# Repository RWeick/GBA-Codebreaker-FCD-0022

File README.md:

# Blaze Xploder SP and Codebreaker FCD-0022
The full schematic, PCB, and flash dumps of the GBA Codebreaker and Xploder SP. Both use the same PCB and CPLD. The original PCB is a 4-layer PCB, though it isn't necessary in order to route everything.

PCB Thickness: 0.8 mm

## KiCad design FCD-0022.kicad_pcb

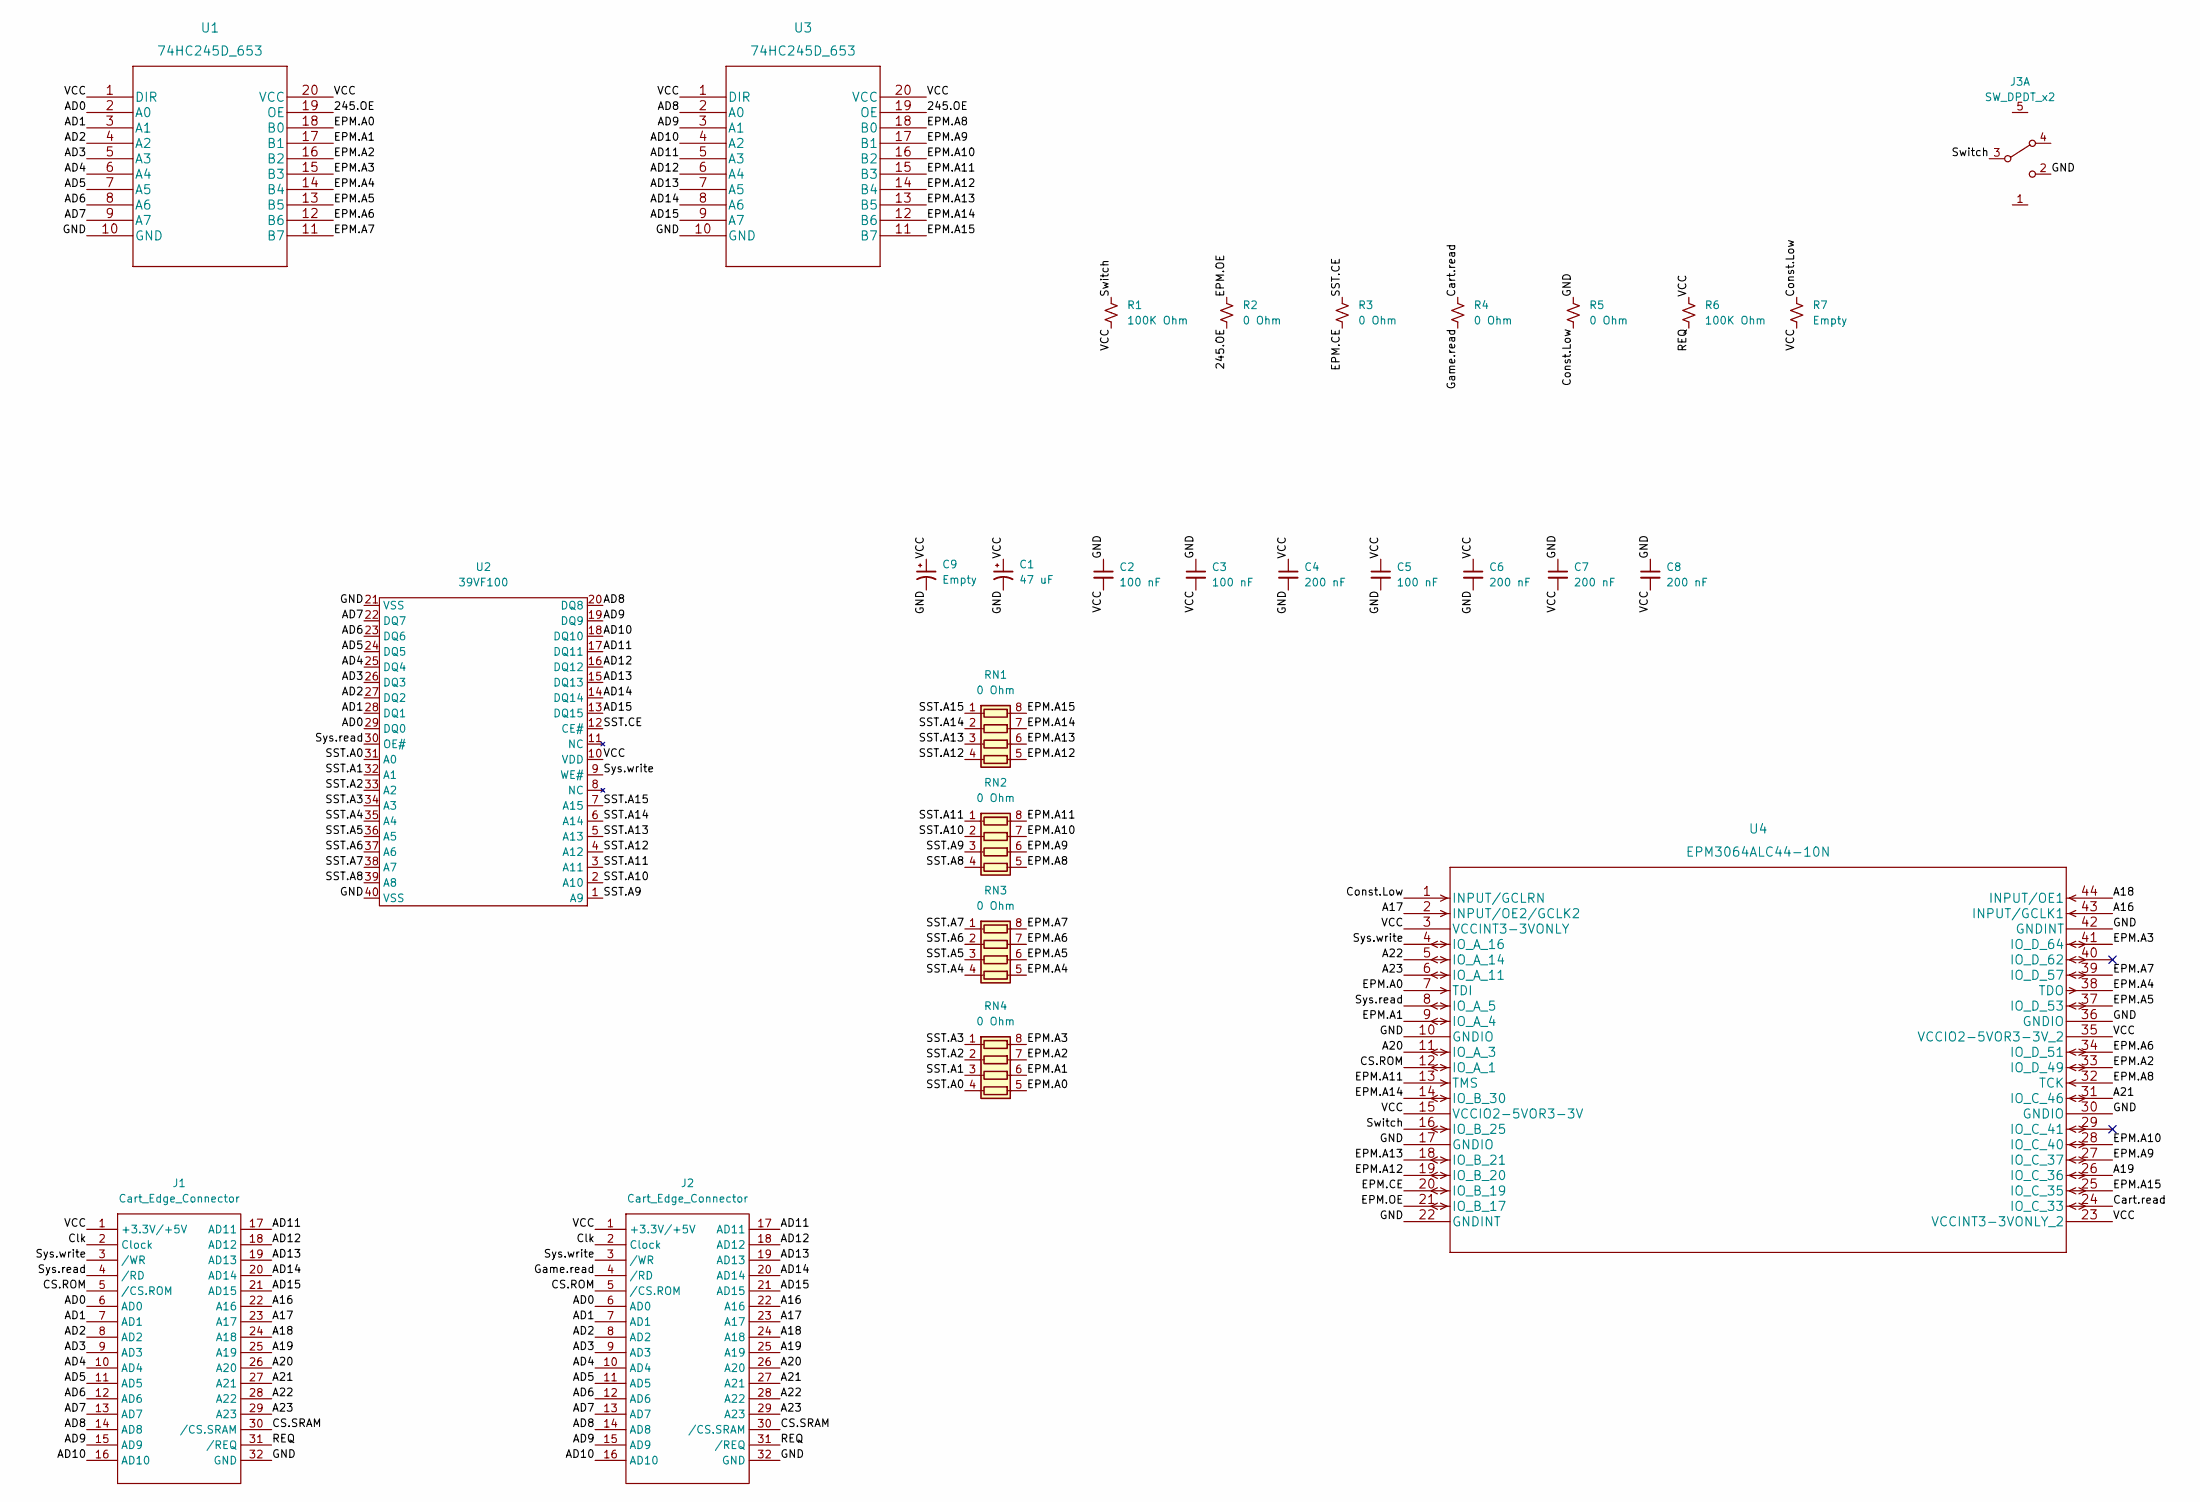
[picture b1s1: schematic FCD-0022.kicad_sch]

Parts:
C1: 47 uF; Codebreaker 47 uF Pad
C2, C3, C5: 100 nF; Codebreaker Cap-Res
C4, C6, C7, C8: 200 nF; Codebreaker Cap-Res
C9: Empty; Codebreaker Cap TH
J1: Cart_Edge_Connector; ACTUAL GAMEBOY EDGE CONNECTOR
J2: Cart_Edge_Connector; Cartridge Slot, GBC
J3: SW_DPDT_x2; Codebreaker Switch
R1, R6: 100K Ohm; Codebreaker Cap-Res
R2, R3, R4, R5: 0 Ohm; Codebreaker Cap-Res
R7: Empty; Codebreaker Cap-Res
RN1, RN2, RN3, RN4: 0 Ohm; R_Array_Convex_4x0603
U1, U3: 74HC245D_653
U2: 39VF100; Codebreaker 39VF100
U4: EPM3064ALC44-10N; PLCC-44

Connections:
/245.OE: R2.2, U1.19 (OE), U3.19 (OE)
/A16: J1.22 (A16), J2.22 (A16), U4.43 (INPUT/GCLK1)
/A17: J1.23 (A17), J2.23 (A17), U4.2 (INPUT/OE2/GCLK2)
/A18: J1.24 (A18), J2.24 (A18), U4.44 (INPUT/OE1)
/A19: J1.25 (A19), J2.25 (A19), U4.26 (IO_C_36)
/A20: J1.26 (A20), J2.26 (A20), U4.11 (IO_A_3)
/A21: J1.27 (A21), J2.27 (A21), U4.31 (IO_C_46)
/A22: J1.28 (A22), J2.28 (A22), U4.5 (IO_A_14)
/A23: J1.29 (A23), J2.29 (A23), U4.6 (IO_A_11)
/AD0: J1.6 (AD0), J2.6 (AD0), U1.2 (A0), U2.29 (DQ0)
/AD1: J1.7 (AD1), J2.7 (AD1), U1.3 (A1), U2.28 (DQ1)
/AD2: J1.8 (AD2), J2.8 (AD2), U1.4 (A2), U2.27 (DQ2)
/AD3: J1.9 (AD3), J2.9 (AD3), U1.5 (A3), U2.26 (DQ3)
/AD4: J1.10 (AD4), J2.10 (AD4), U1.6 (A4), U2.25 (DQ4)
/AD5: J1.11 (AD5), J2.11 (AD5), U1.7 (A5), U2.24 (DQ5)
/AD6: J1.12 (AD6), J2.12 (AD6), U1.8 (A6), U2.23 (DQ6)
/AD7: J1.13 (AD7), J2.13 (AD7), U1.9 (A7), U2.22 (DQ7)
/AD8: J1.14 (AD8), J2.14 (AD8), U2.20 (DQ8), U3.2 (A0)
/AD9: J1.15 (AD9), J2.15 (AD9), U2.19 (DQ9), U3.3 (A1)
/AD10: J1.16 (AD10), J2.16 (AD10), U2.18 (DQ10), U3.4 (A2)
/AD11: J1.17 (AD11), J2.17 (AD11), U2.17 (DQ11), U3.5 (A3)
/AD12: J1.18 (AD12), J2.18 (AD12), U2.16 (DQ12), U3.6 (A4)
/AD13: J1.19 (AD13), J2.19 (AD13), U2.15 (DQ13), U3.7 (A5)
/AD14: J1.20 (AD14), J2.20 (AD14), U2.14 (DQ14), U3.8 (A6)
/AD15: J1.21 (AD15), J2.21 (AD15), U2.13 (DQ15), U3.9 (A7)
/CS.ROM: J1.5 (/CS.ROM), J2.5 (/CS.ROM), U4.12 (IO_A_1)
/CS.SRAM: J1.30 (/CS.SRAM), J2.30 (/CS.SRAM)
/Cart.read: R4.1, U4.24 (IO_C_33)
/Clk: J1.2 (Clock), J2.2 (Clock)
/Const.Low: R5.2, R7.1, U4.1 (INPUT/GCLRN)
/EPM.A0: RN4.5 (R4.2), U1.18 (B0), U4.7 (TDI)
/EPM.A1: RN4.6 (R3.2), U1.17 (B1), U4.9 (IO_A_4)
/EPM.A2: RN4.7 (R2.2), U1.16 (B2), U4.33 (IO_D_49)
/EPM.A3: RN4.8 (R1.2), U1.15 (B3), U4.41 (IO_D_64)
/EPM.A4: RN3.5 (R4.2), U1.14 (B4), U4.38 (TDO)
/EPM.A5: RN3.6 (R3.2), U1.13 (B5), U4.37 (IO_D_53)
/EPM.A6: RN3.7 (R2.2), U1.12 (B6), U4.34 (IO_D_51)
/EPM.A7: RN3.8 (R1.2), U1.11 (B7), U4.39 (IO_D_57)
/EPM.A8: RN2.5 (R4.2), U3.18 (B0), U4.32 (TCK)
/EPM.A9: RN2.6 (R3.2), U3.17 (B1), U4.27 (IO_C_37)
/EPM.A10: RN2.7 (R2.2), U3.16 (B2), U4.28 (IO_C_40)
/EPM.A11: RN2.8 (R1.2), U3.15 (B3), U4.13 (TMS)
/EPM.A12: RN1.5 (R4.2), U3.14 (B4), U4.19 (IO_B_20)
/EPM.A13: RN1.6 (R3.2), U3.13 (B5), U4.18 (IO_B_21)
/EPM.A14: RN1.7 (R2.2), U3.12 (B6), U4.14 (IO_B_30)
/EPM.A15: RN1.8 (R1.2), U3.11 (B7), U4.25 (IO_C_35)
/EPM.CE: R3.2, U4.20 (IO_B_19)
/EPM.OE: R2.1, U4.21 (IO_B_17)
/GND: C1.2, C2.1, C3.1, C4.2, C5.2, C6.2, C7.1, C8.1, C9.2, J1.32 (GND), J2.32 (GND), J3.2 (C), R5.1, U1.10 (GND), U2.21 (VSS), U2.40 (VSS), U3.10 (GND), U4.10 (GNDIO), U4.17 (GNDIO), U4.22 (GNDINT), U4.30 (GNDIO), U4.36 (GNDIO), U4.42 (GNDINT)
/Game.read: J2.4 (/RD), R4.2
/REQ: J1.31 (/REQ), J2.31 (/REQ), R6.2
/SST.A0: RN4.4 (R4.1), U2.31 (A0)
/SST.A1: RN4.3 (R3.1), U2.32 (A1)
/SST.A2: RN4.2 (R2.1), U2.33 (A2)
/SST.A3: RN4.1 (R1.1), U2.34 (A3)
/SST.A4: RN3.4 (R4.1), U2.35 (A4)
/SST.A5: RN3.3 (R3.1), U2.36 (A5)
/SST.A6: RN3.2 (R2.1), U2.37 (A6)
/SST.A7: RN3.1 (R1.1), U2.38 (A7)
/SST.A8: RN2.4 (R4.1), U2.39 (A8)
/SST.A9: RN2.3 (R3.1), U2.1 (A9)
/SST.A10: RN2.2 (R2.1), U2.2 (A10)
/SST.A11: RN2.1 (R1.1), U2.3 (A11)
/SST.A12: RN1.4 (R4.1), U2.4 (A12)
/SST.A13: RN1.3 (R3.1), U2.5 (A13)
/SST.A14: RN1.2 (R2.1), U2.6 (A14)
/SST.A15: RN1.1 (R1.1), U2.7 (A15)
/SST.CE: R3.1, U2.12 (CE#)
/Switch: J3.3 (B), R1.1, U4.16 (IO_B_25)
/Sys.read: J1.4 (/RD), U2.30 (OE#), U4.8 (IO_A_5)
/Sys.write: J1.3 (/WR), J2.3 (/WR), U2.9 (WE#), U4.4 (IO_A_16)
/VCC: C1.1, C2.2, C3.2, C4.1, C5.1, C6.1, C7.2, C8.2, C9.1, J1.1 (+3.3V/+5V), J2.1 (+3.3V/+5V), R1.2, R6.1, R7.2, U1.1 (DIR), U1.20 (VCC), U2.10 (VDD), U3.1 (DIR), U3.20 (VCC), U4.3 (VCCINT3-3VONLY), U4.15 (VCCIO2-5VOR3-3V), U4.23 (VCCINT3-3VONLY_2), U4.35 (VCCIO2-5VOR3-3V_2)

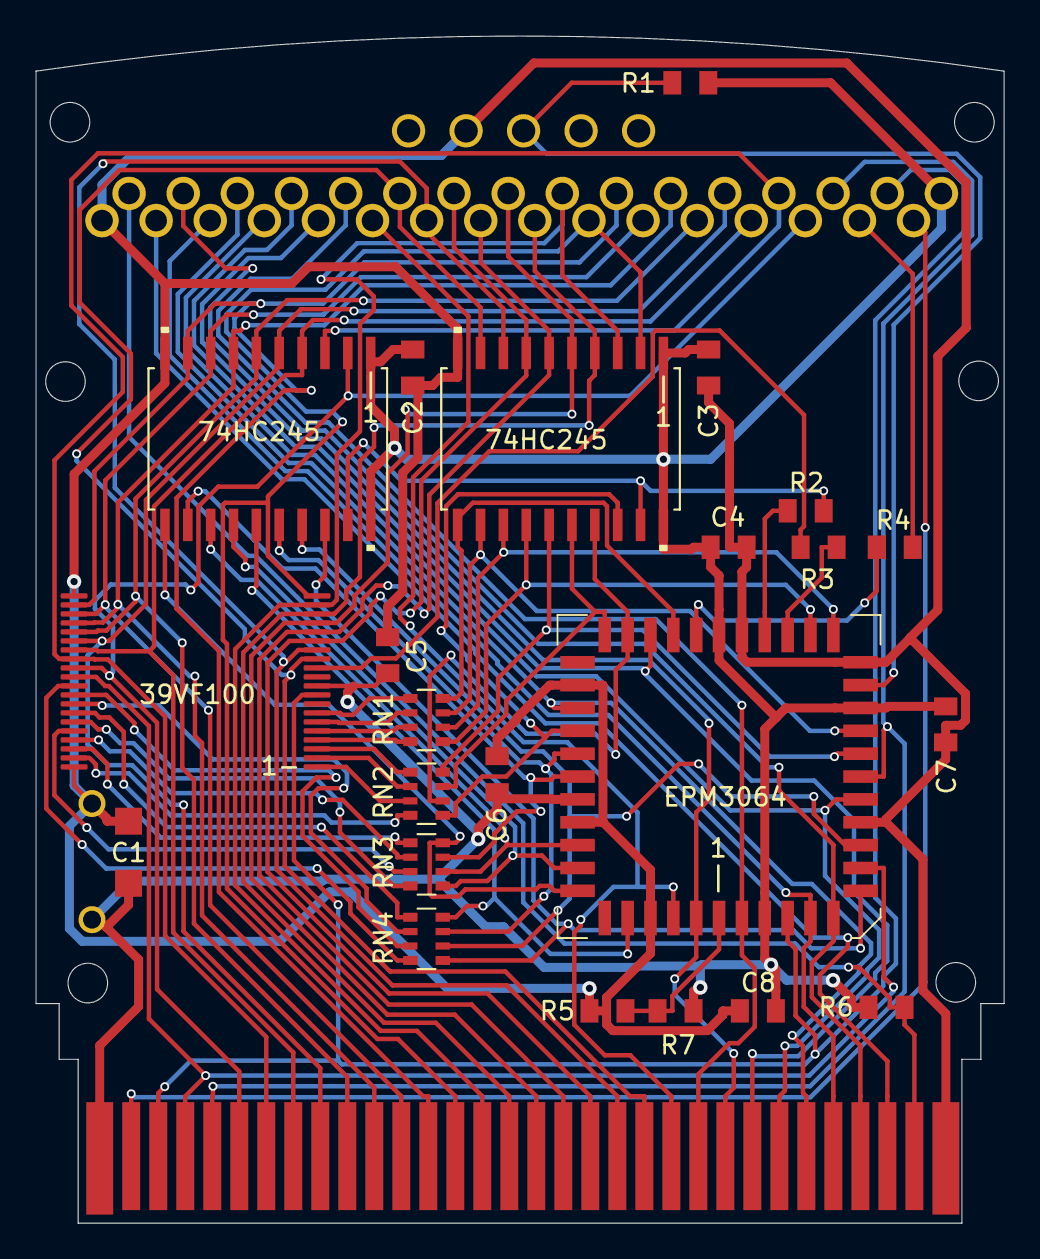
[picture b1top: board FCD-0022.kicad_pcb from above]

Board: 2 copper layers, 53.8 x 66.0 mm, 33 parts (0 on the bottom side), 72 nets.

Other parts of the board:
H1, H2, H3, H4, H5, H6: MountingHole_2.2mm_M2

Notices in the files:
parts and their libraries:
Copyright 2021 Accelerated Designs. All rights reserved.
